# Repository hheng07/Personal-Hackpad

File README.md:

# Personal-Hackpad
Four arrow keys to use either for gaming or to utilize as shortcut keys. Also implemented an EC11 encoder for customizable actions like volume control.

### Challenges
At first I was using FreeCad, but I was having trouble fighting the different restraints, so I had to switch over to Fusion360's free trial to ease up on my stress levels. 

### Specifications

BOM: 
- 4x Cherry MX Switches
- 2x SK6812 MINI Leds
- 1x XIAO RP2040
- 4x Blank DSA Keycaps
- 4x M3x16 Bolt
- 4x M3 Heatset
- 1x EC11 Rotary Encoder
- 1x 3D prints of case and cover

Schematic            |  PCB         
:-------------------------:|:-------------------------:
 |

|Bottom             | Top             | Combined            |
|:-------------------------:|:-------------------------:|:-------------------------:|
  |  |

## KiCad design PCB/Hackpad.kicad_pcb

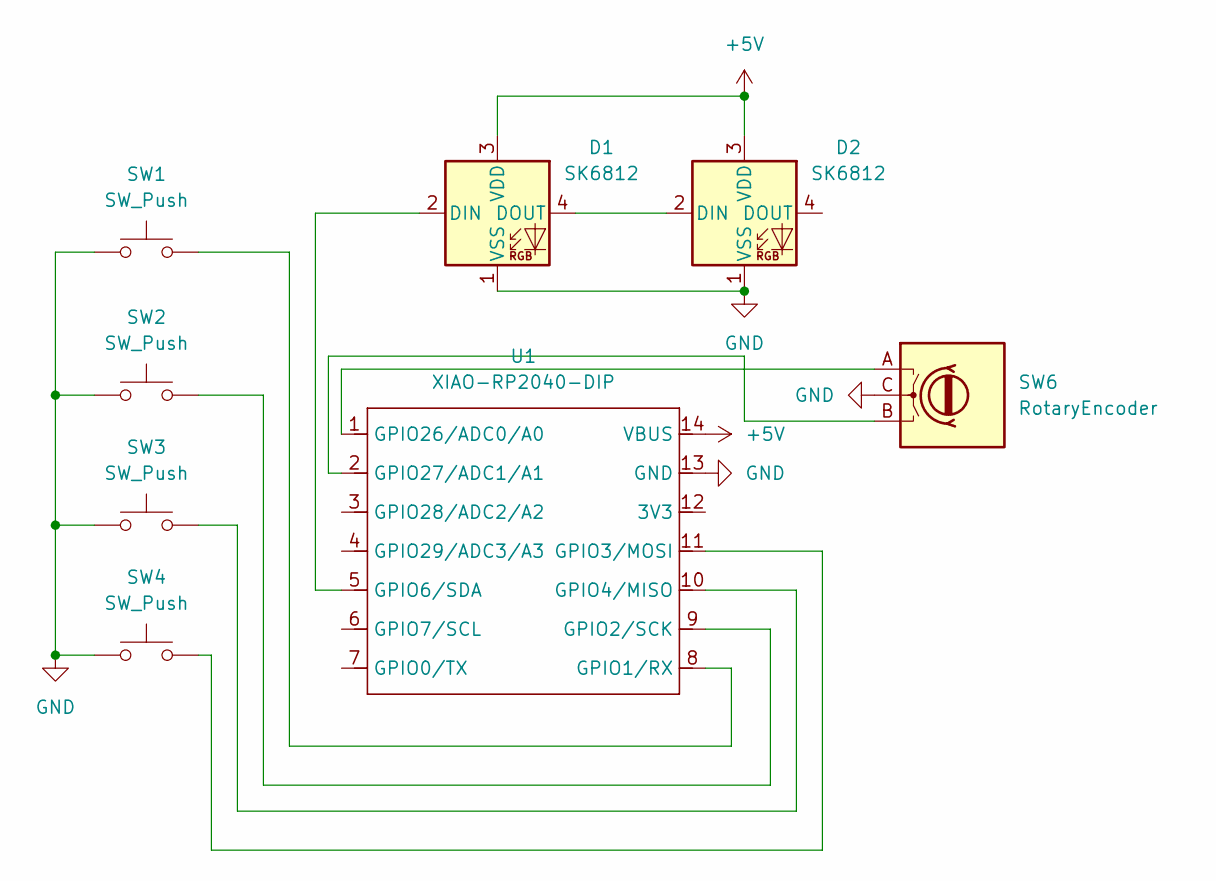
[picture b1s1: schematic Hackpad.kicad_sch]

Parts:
D1, D2: SK6812; MX_SK6812MINI-E_REV
SW1, SW2, SW3, SW4: SW_Push; SW_Cherry_MX_1.00u_PCB
SW6: RotaryEncoder; RotaryEncoder_Alps_EC11E_Vertical_H20mm
U1: XIAO-RP2040-DIP

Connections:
+5V: D1.3 (VDD), D2.3 (VDD), U1.14 (VBUS)
GND: D1.1 (VSS), D2.1 (VSS), SW1.1, SW2.1, SW3.1, SW4.1, SW6.C, U1.13 (GND)
unnamed: D1.2 (DIN), U1.5 (GPIO6/SDA)
unnamed: D1.4 (DOUT), D2.2 (DIN)
unnamed: SW1.2, U1.8 (GPIO1/RX)
unnamed: SW2.2, U1.9 (GPIO2/SCK)
unnamed: SW4.2, U1.11 (GPIO3/MOSI)
unnamed: SW3.2, U1.10 (GPIO4/MISO)
unnamed: SW6.A, U1.1 (GPIO26/ADC0/A0)
unnamed: SW6.B, U1.2 (GPIO27/ADC1/A1)

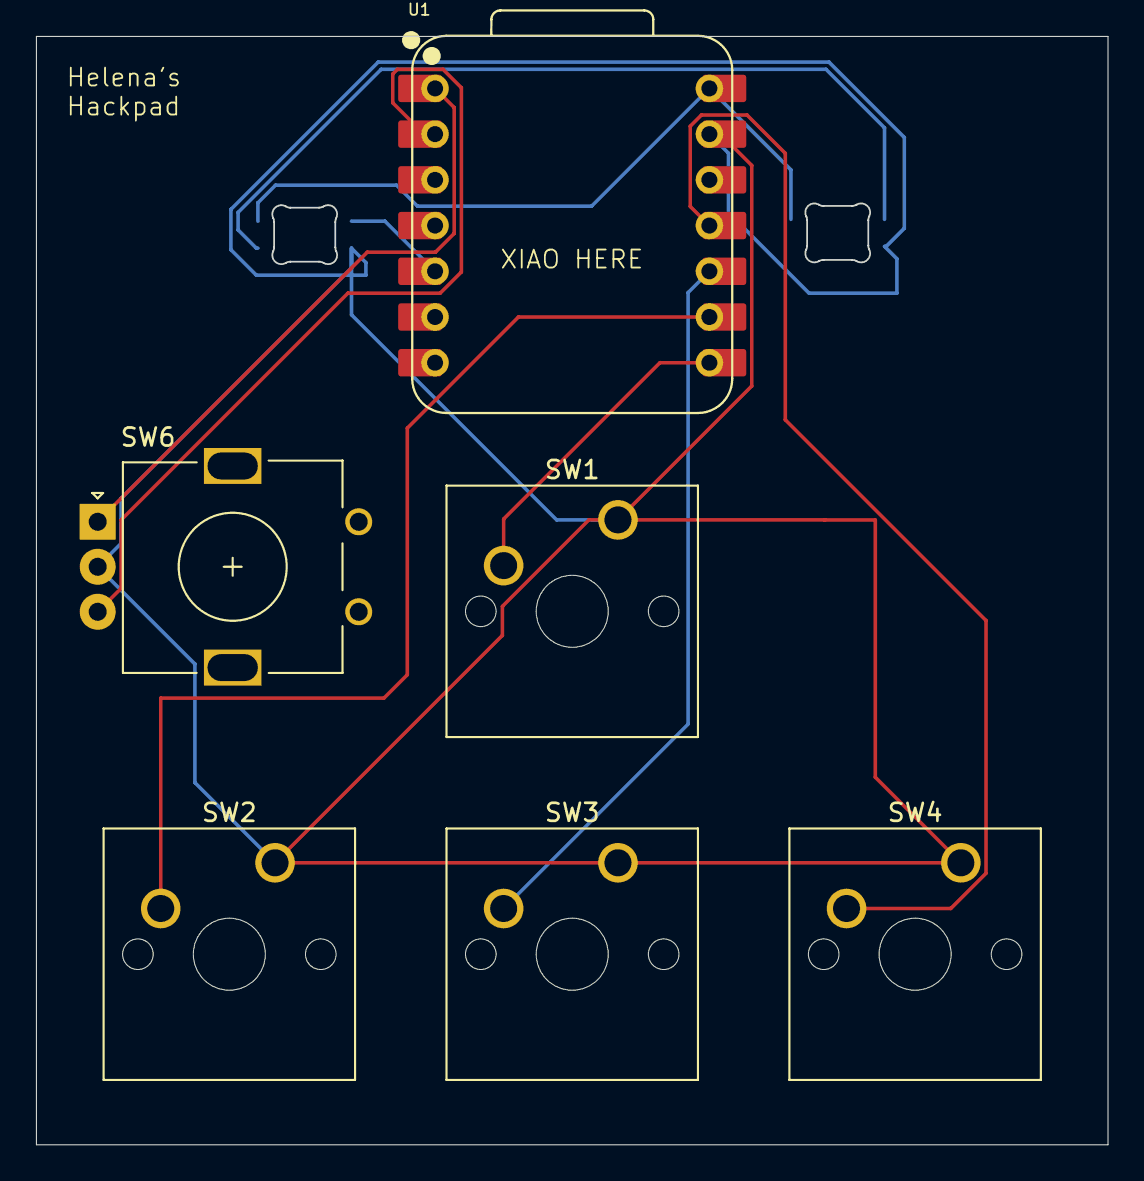
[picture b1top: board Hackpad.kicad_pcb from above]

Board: 2 copper layers, 59.5 x 61.5 mm, 8 parts (0 on the bottom side), 10 nets.

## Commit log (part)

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2026-02-04 Create CAD
2026-02-04 Update CAD
2026-02-04 Create PCB
2026-02-04 Create pcbs
2026-02-04 Create cads
2026-02-04 Create firmware
2026-02-05 Create production
